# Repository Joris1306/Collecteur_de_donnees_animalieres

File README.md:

**(English part below)**

# Piège Caméra avec Classification Animale par IA (De A à Z)

Bienvenue sur le dépôt officiel du projet **Piège Photographique avec Classification Animale par IA**. Nous sommes une équipe de six étudiants ingénieurs de **Polytech Nantes** ayant dédié une année universitaire complète à la conception, fabrication et au déploiement de cette solution open-source.

Ce projet a été réalisé en partenariat étroit avec la **Mairie de Saint-Mars-du-Désert** et ses associations partenaires : le **WWF**, la **LPO** (Ligue pour la Protection des Oiseaux) et **Natura 2000**, qui ont gracieusement financé et soutenu notre démarche.

---

## 🌍 Contexte & Objectifs

La préservation de la biodiversité et la conservation des espèces sont des enjeux plus que jamais urgents. Pour protéger efficacement notre faune locale, il est indispensable de mieux la connaître et de suivre son évolution.

C'est là tout l'enjeu de notre projet : concevoir de A à Z un **piège photographique autonome couplé à une intelligence artificielle de classification**. Les données capturées sont envoyées vers un serveur centralisé et rendues accessibles à travers une interface web intuitive.

**Le but ultime :** Automatiser le recensement de la faune locale pour enrichir l'**ABC (Atlas de la Biodiversité Communale)**.

---

## 🛠️ Architecture du Projet & Contenu du Dépôt

Ce repository rassemble l'intégralité des ressources nécessaires pour reproduire et améliorer notre travail :

* **⚡ Électronique & Conception :** Les codes ESP32 du piège caméra, Modélisations 3D du boîtier, schémas électriques et liste complète des composants (BOM).
* **🧠 Intelligence Artificielle :** Algorithmes et scripts d'apprentissage pour la détection et la classification embarquée des animaux.
* **🌐 Serveur & Interface Web :** Architecture backend pour le stockage des données et code de l'interface utilisateur.
* **📄 Documentation :** Rapports techniques détaillés pour ceux qui souhaitent approfondir les choix d'ingénierie et méthodologies du projet.

---

## 🤝 Remerciements

Nous tenons à exprimer notre profonde gratitude envers :
* Nos professeurs de **Polytech Nantes** pour leur encadrement et leurs précieux conseils.
* La **Mairie de Saint-Mars-du-Désert** ainsi que les associations partenaires pour leur confiance et leur soutien financier.
* Les professionnels et chercheurs du milieu de l'environnement qui ont répondu avec enthousiasme à nos questions, prouvant que la recherche pour la biodiversité est avant tout une grande famille.

Nous passons aujourd'hui le flambeau aux futurs groupes d'étudiants passionnés. Ce projet est entièrement **open-source**, et nous avons hâte de voir comment vous saurez le faire évoluer !

---

## 🔗 Démo en Ligne

Découvrez les données récoltées et les résultats de la classification en temps réel :
👉 **[Accéder à l'Interface Web du Projet](http://90.59.66.6:5050)**

***

# Camera Trap with AI Animal Classification (From Scratch)

Welcome to the official repository for the **Camera Trap with AI Animal Classification** project. We are a team of six engineering students from **Polytech Nantes** who dedicated a full academic year to designing, building, and deploying this open-source solution. 

This project was developed in close partnership with the **Municipality of Saint-Mars-du-Désert** and its environmental partners: **WWF**, **LPO** (League for the Protection of Birds), and **Natura 2000**, who generously funded and supported our work.

---

## 🌍 Context & Vision

Biodiversity and species conservation have never been more critical. To protect our local wildlife effectively, we must first monitor and understand it. 

Our project tackles this challenge from the ground up by building an autonomous **Camera Trap paired with an AI-driven animal classification model**. Captured footage is securely transmitted to a central server and made accessible through an intuitive web interface. 

**The ultimate goal:** Automate the inventory and monitoring of local fauna to support the **ABC (Atlas de la Biodiversité Communale)** initiatives.

---

## 🛠️ Project Architecture & Repository Structure

This repository contains everything needed to replicate, understand, and build upon our work from scratch:

* **⚡ Hardware & Electronics:** ESP32 principal code, 3D CAD modeling files for the enclosure, electrical schematics, and a complete Bill of Materials (BOM).
* **🧠 Artificial Intelligence:** Embedded AI models and scripts optimized for real-time edge animal classification.
* **🌐 Server & Web Interface:** Backend architecture for data collection and frontend dashboard code for visualization.
* **📄 Documentation:** Deep-dive technical reports detailing our engineering choices, challenges, and methodologies.

---

## 🤝 Acknowledgments

We would like to extend our deepest gratitude to:
* Our supervising professors at **Polytech Nantes** for their invaluable academic guidance.
* The **Municipality of Saint-Mars-du-Désert** and its partner associations for their trust and financial backing.
* The biodiversity and research professionals who generously shared their expertise with us. Your willingness to help proves that wildlife conservation is a truly collaborative family.

We now pass the torch to future generations of passionate students. This project is entirely **open-source**, and we look forward to seeing how you adapt, improve, and scale it!

---

## 🔗 Live Demo

Explore the captured data and classification metrics live here:
👉 **[Access the Web Interface Dashboard](http://90.59.66.6:5050)**

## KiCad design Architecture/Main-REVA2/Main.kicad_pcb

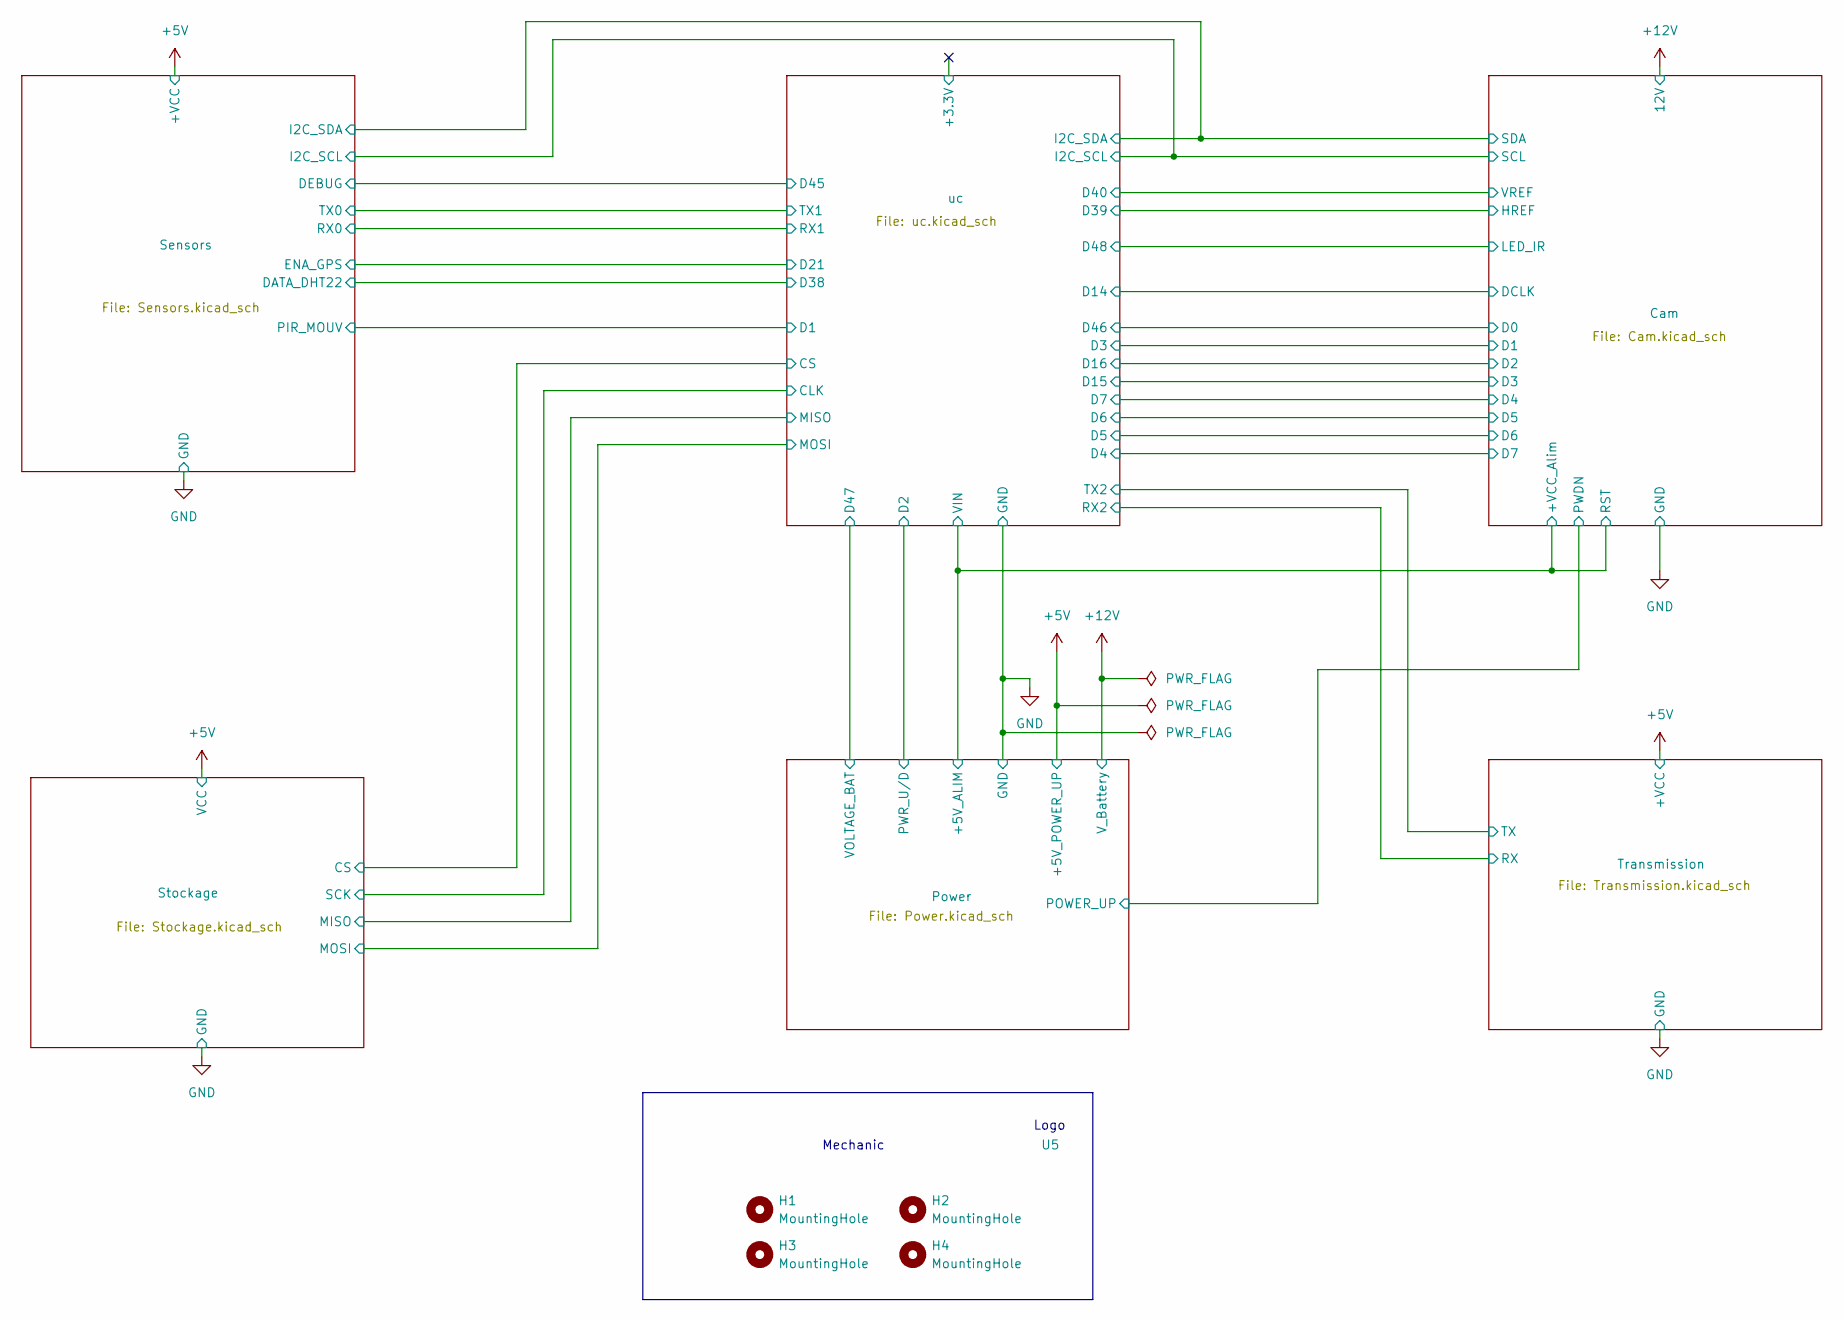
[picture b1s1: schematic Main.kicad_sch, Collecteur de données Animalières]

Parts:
H1, H2, H3, H4: MountingHole; MountingHole_2.2mm_M2_ISO7380
U5: Logo_20_20

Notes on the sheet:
Mechanic
Logo

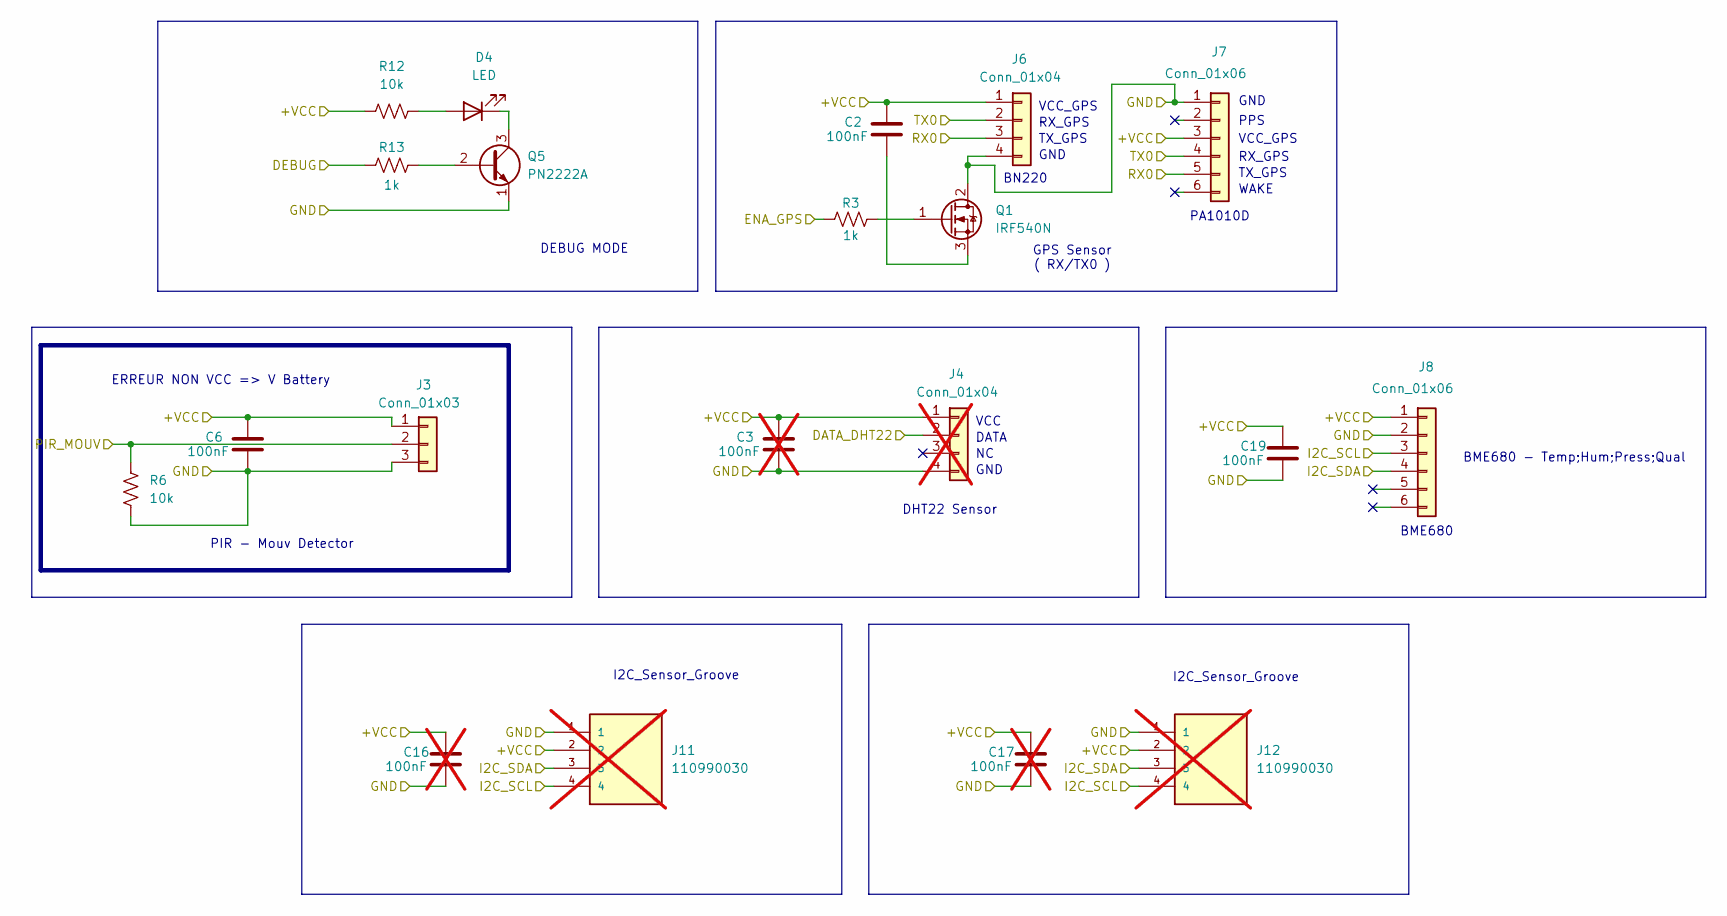
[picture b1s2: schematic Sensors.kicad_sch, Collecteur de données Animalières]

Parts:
C2, C6, C19: 100nF; C_Disc_D5.0mm_W2.5mm_P5.00mm
C3, C16, C17: 100nF; C_Disc_D5.0mm_W2.5mm_P5.00mm; not fitted
D4: LED; LED_D5.0mm
J3: Conn_01x03; PinHeader_1x03_P2.54mm_Vertical
J4: Conn_01x04; PinHeader_1x04_P2.54mm_Vertical; not fitted
J6: Conn_01x04; PinHeader_1x04_P2.54mm_Vertical
J7, J8: Conn_01x06; PinHeader_1x06_P2.54mm_Vertical
J11, J12: 110990030; Grove; PARTREV A; not fitted
Q1: IRF540N; TO-220-3_Vertical
Q5: PN2222A; TO-92_Inline
R3, R13: 1k; R_Axial_DIN0207_L6.3mm_D2.5mm_P10.16mm_Horizontal
R6, R12: 10k; R_Axial_DIN0207_L6.3mm_D2.5mm_P10.16mm_Horizontal

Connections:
+5V: C2.1, C3.1, C6.1, C16.1, C17.1, C19.1, J3.1, J4.1, J6.1, J7.3, J8.1, J11.2, J12.2, R12.1; also elsewhere on the board
/Cam/SCL: J8.3, J11.4, J12.4; also elsewhere on the board
/Cam/SDA: J8.4, J11.3, J12.3; also elsewhere on the board
/Sensors/DATA_DHT22: J4.2; also elsewhere on the board
/Sensors/DEBUG: R13.1; also elsewhere on the board
/Sensors/ENA_GPS: R3.1; also elsewhere on the board
/Sensors/PIR_MOUV: J3.2, R6.1; also elsewhere on the board
/Sensors/RX0: J6.3, J7.5; also elsewhere on the board
/Sensors/TX0: J6.2, J7.4; also elsewhere on the board
GND: C3.2, C6.2, C16.2, C17.2, C19.2, J3.3, J4.4, J6.4, J7.1, J8.2, J11.1, J12.1, Q1.2 (D), Q5.1 (E), R6.2; also elsewhere on the board
unnamed: D4.2 (A), R12.2
unnamed: D4.1 (K), Q5.3 (C)
unnamed: Q1.1 (G), R3.2
unnamed: C2.2, Q1.3 (S)
unnamed: Q5.2 (B), R13.2

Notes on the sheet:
RX_GPS
I2C_Sensor_Groove
PA1010D
VCC
GND
VCC_GPS
PIR - Mouv Detector
DATA
TX_GPS
DEBUG MODE
BME680
BN220
ERREUR NON VCC => V Battery
PPS
GPS Sensor ( RX/TX0 )
WAKE
BME680 - Temp;Hum;Press;Qual
DHT22 Sensor

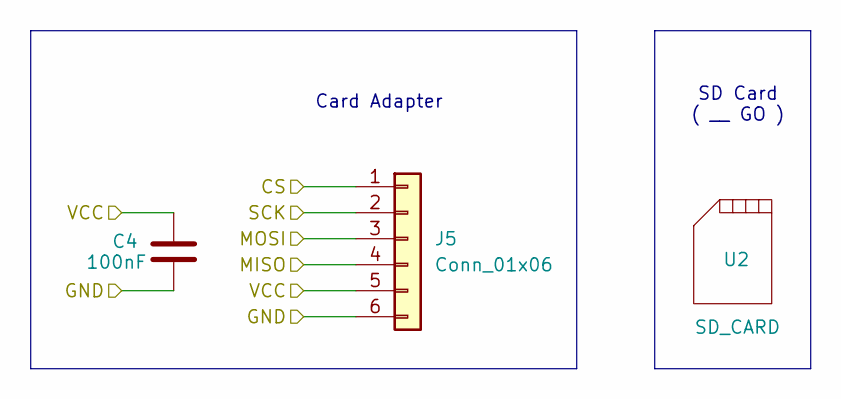
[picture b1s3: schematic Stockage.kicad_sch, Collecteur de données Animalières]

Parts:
C4: 100nF; C_Disc_D5.0mm_W2.5mm_P5.00mm
J5: Conn_01x06; PinHeader_1x06_P2.54mm_Vertical
U2: SD_CARD

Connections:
+5V: C4.1, J5.5; also elsewhere on the board
/Stockage/CS: J5.1; also elsewhere on the board
/Stockage/MISO: J5.4; also elsewhere on the board
/Stockage/MOSI: J5.3; also elsewhere on the board
/Stockage/SCK: J5.2; also elsewhere on the board
GND: C4.2, J5.6; also elsewhere on the board

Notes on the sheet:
SD Card ( __ GO )
Card Adapter

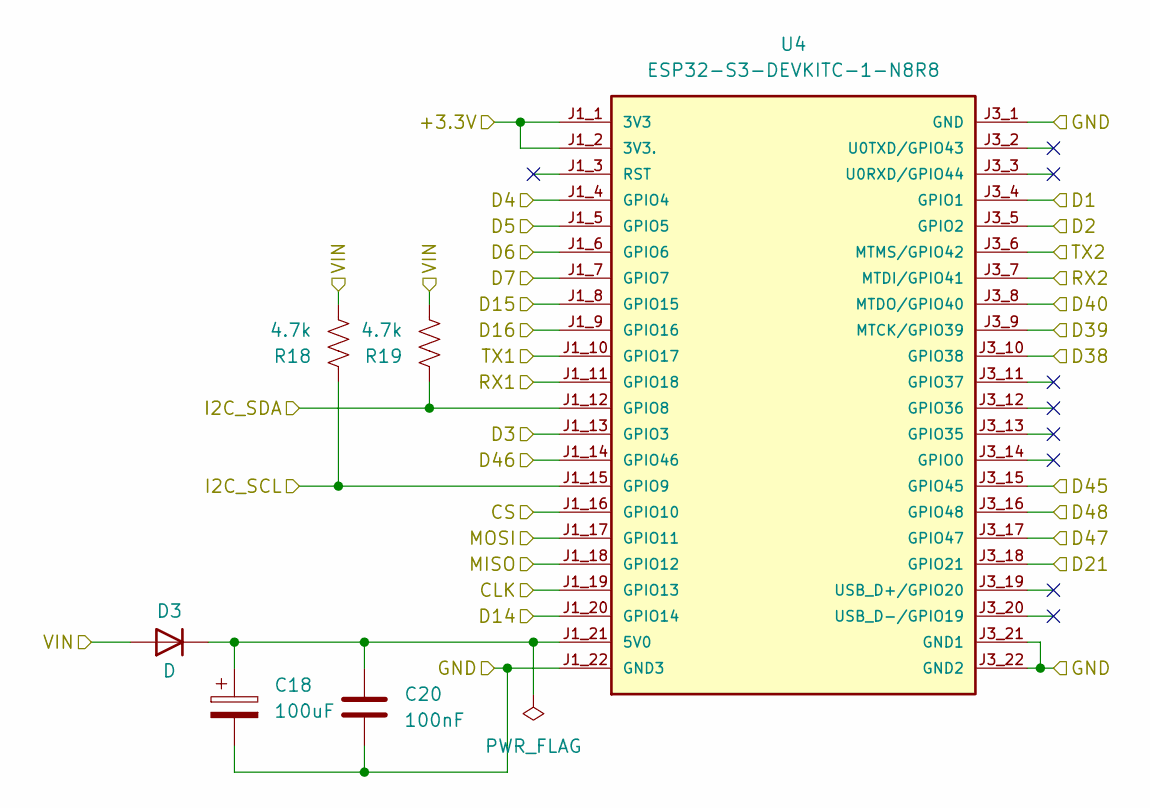
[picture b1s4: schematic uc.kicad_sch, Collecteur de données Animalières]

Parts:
C18: 100uF; C_Radial_D10.0mm_H16.0mm_P5.00mm
C20: 100nF; C_Disc_D5.0mm_W2.5mm_P5.00mm
D3: D; D_DO-35_SOD27_P7.62mm_Horizontal
R18, R19: 4.7k; R_Axial_DIN0207_L6.3mm_D2.5mm_P10.16mm_Horizontal
U4: ESP32-S3-DEVKITC-1-N8R8

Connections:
/Cam/+VCC_Alim: D3.2 (A), R18.2, R19.2; also elsewhere on the board
/Cam/D0: U4.J1_14 (GPIO46); also elsewhere on the board
/Cam/D1: U4.J1_13 (GPIO3); also elsewhere on the board
/Cam/D2: U4.J1_9 (GPIO16); also elsewhere on the board
/Cam/D3: U4.J1_8 (GPIO15); also elsewhere on the board
/Cam/D4: U4.J1_7 (GPIO7); also elsewhere on the board
/Cam/D5: U4.J1_6 (GPIO6); also elsewhere on the board
/Cam/D6: U4.J1_5 (GPIO5); also elsewhere on the board
/Cam/D7: U4.J1_4 (GPIO4); also elsewhere on the board
/Cam/DCLK: U4.J1_20 (GPIO14); also elsewhere on the board
/Cam/HREF: U4.J3_9 (MTCK/GPIO39); also elsewhere on the board
/Cam/LED_IR: U4.J3_16 (GPIO48); also elsewhere on the board
/Cam/SCL: R18.1, U4.J1_15 (GPIO9); also elsewhere on the board
/Cam/SDA: R19.1, U4.J1_12 (GPIO8); also elsewhere on the board
/Cam/VREF: U4.J3_8 (MTDO/GPIO40); also elsewhere on the board
/Power/PWR_U/D: U4.J3_5 (GPIO2); also elsewhere on the board
/Power/VOLTAGE_BAT: U4.J3_17 (GPIO47); also elsewhere on the board
/Sensors/DATA_DHT22: U4.J3_10 (GPIO38); also elsewhere on the board
/Sensors/DEBUG: U4.J3_15 (GPIO45); also elsewhere on the board
/Sensors/ENA_GPS: U4.J3_18 (GPIO21); also elsewhere on the board
/Sensors/PIR_MOUV: U4.J3_4 (GPIO1); also elsewhere on the board
/Sensors/RX0: U4.J1_11 (GPIO18); also elsewhere on the board
/Sensors/TX0: U4.J1_10 (GPIO17); also elsewhere on the board
/Stockage/CS: U4.J1_16 (GPIO10); also elsewhere on the board
/Stockage/MISO: U4.J1_18 (GPIO12); also elsewhere on the board
/Stockage/MOSI: U4.J1_17 (GPIO11); also elsewhere on the board
/Stockage/SCK: U4.J1_19 (GPIO13); also elsewhere on the board
/Transmission/RX: U4.J3_7 (MTDI/GPIO41); also elsewhere on the board
/Transmission/TX: U4.J3_6 (MTMS/GPIO42); also elsewhere on the board
/uc/+3.3V: U4.J1_1 (3V3), U4.J1_2 (3V3.)
GND: C18.2, C20.2, U4.J1_22 (GND3), U4.J3_1 (GND), U4.J3_21 (GND1), U4.J3_22 (GND2); also elsewhere on the board
unnamed: C18.1, C20.1, D3.1 (K), U4.J1_21 (5V0)

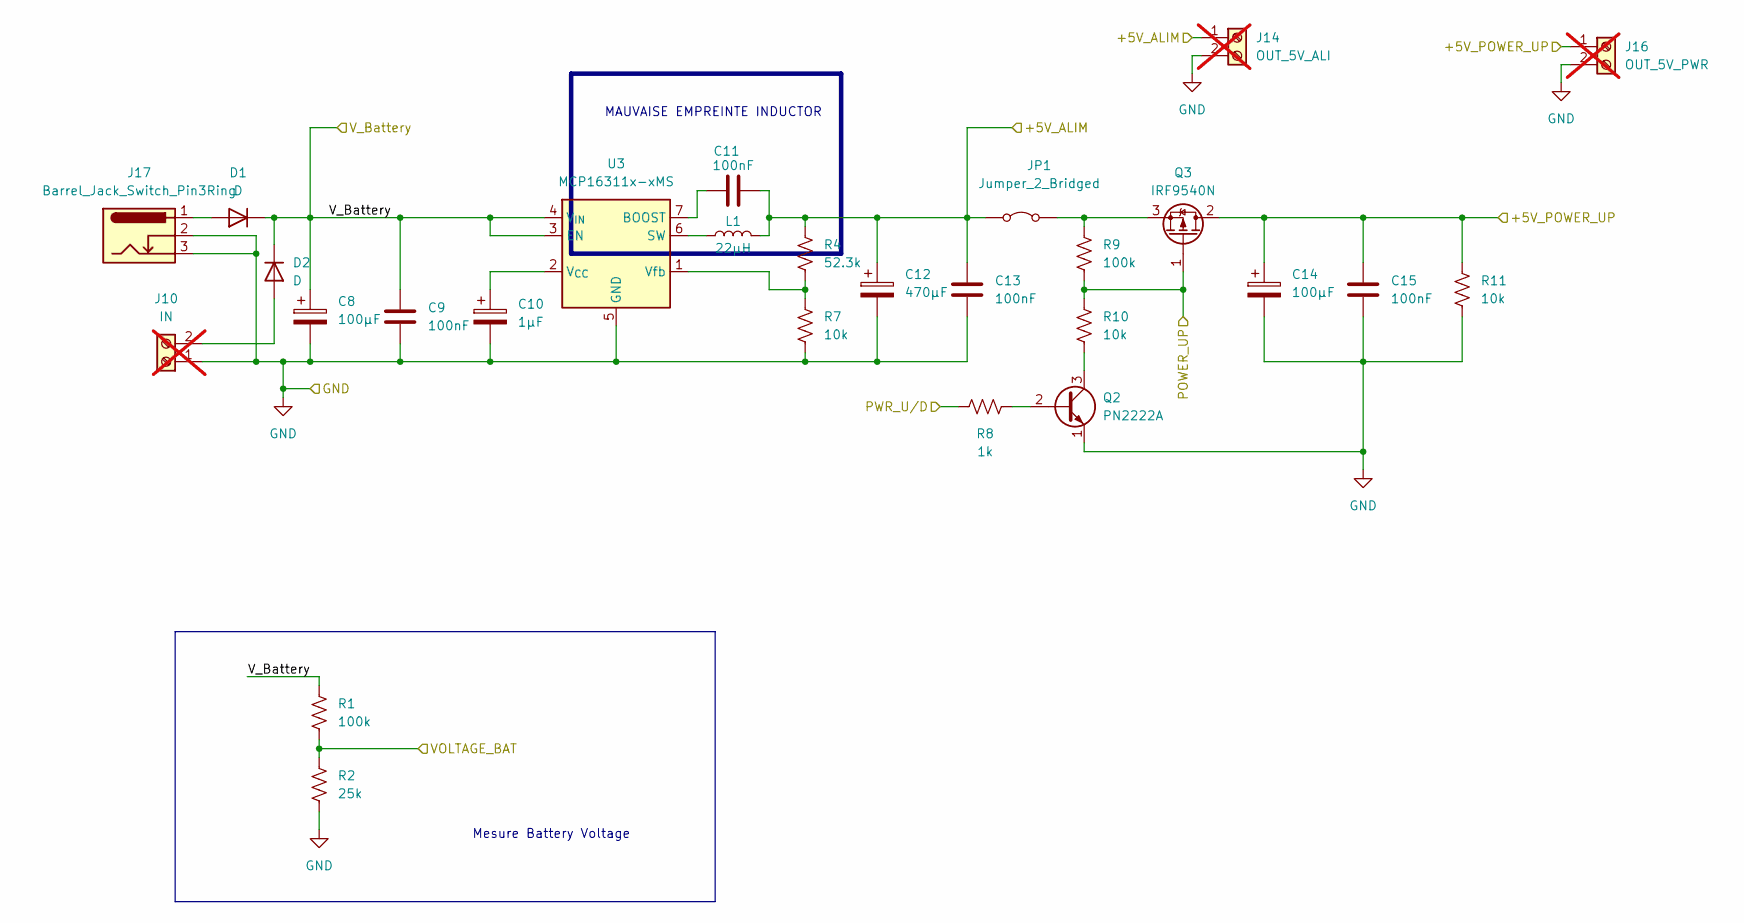
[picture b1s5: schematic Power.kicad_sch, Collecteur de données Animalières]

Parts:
C8, C14: 100µF; C_Radial_D10.0mm_H16.0mm_P5.00mm
C9, C11, C13, C15: 100nF; C_Disc_D5.0mm_W2.5mm_P5.00mm
C10: 1µF; C_Radial_D10.0mm_H16.0mm_P5.00mm
C12: 470µF; C_Radial_D10.0mm_H16.0mm_P5.00mm
D1, D2: D; D_DO-35_SOD27_P7.62mm_Horizontal
J10: IN; PinHeader_1x02_P2.54mm_Vertical; not fitted
J14: OUT_5V_ALI; PinHeader_1x02_P2.54mm_Vertical; not fitted
J16: OUT_5V_PWR; PinHeader_1x02_P2.54mm_Vertical; not fitted
J17: Barrel_Jack_Switch_Pin3Ring; BarrelJack_Horizontal
JP1: Jumper_2_Bridged; PinHeader_1x02_P2.54mm_Vertical
L1: 22µH; R_Axial_DIN0207_L6.3mm_D2.5mm_P10.16mm_Horizontal
Q2: PN2222A; TO-92_Inline
Q3: IRF9540N; TO-220-3_Vertical
R1, R9: 100k; R_Axial_DIN0207_L6.3mm_D2.5mm_P10.16mm_Horizontal
R2: 25k; R_Axial_DIN0207_L6.3mm_D2.5mm_P10.16mm_Horizontal
R4: 52.3k; R_Axial_DIN0207_L6.3mm_D2.5mm_P10.16mm_Horizontal
R7, R10, R11: 10k; R_Axial_DIN0207_L6.3mm_D2.5mm_P10.16mm_Horizontal
R8: 1k; R_Axial_DIN0207_L6.3mm_D2.5mm_P10.16mm_Horizontal
U3: MCP16311x-xMS; MSOP-8_3x3mm_P0.65mm

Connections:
+5V: C14.1, C15.1, J16.1, Q3.2 (D), R11.1; also elsewhere on the board
+12V: C8.1, C9.1, D1.1 (K), D2.1 (K), R1.1, U3.3 (EN), U3.4 (V_{IN}); also elsewhere on the board
/Cam/+VCC_Alim: C11.2, C12.1, C13.1, J14.1, JP1.1 (A), L1.2, R4.1; also elsewhere on the board
/Cam/PWDN: Q3.1 (G), R9.2, R10.1; also elsewhere on the board
/Power/PWR_U/D: R8.1; also elsewhere on the board
/Power/VOLTAGE_BAT: R1.2, R2.1; also elsewhere on the board
GND: C8.2, C9.2, C10.2, C12.2, C13.2, C14.2, C15.2, J10.1, J14.2, J16.2, J17.2, J17.3, Q2.1 (E), R2.2, R7.2, R11.2, U3.5 (GND), U3.8 (GND); also elsewhere on the board
unnamed: D1.2 (A), J17.1
unnamed: D2.2 (A), J10.2
unnamed: JP1.2 (B), Q3.3 (S), R9.1
unnamed: Q2.2 (B), R8.2
unnamed: Q2.3 (C), R10.2
unnamed: C11.1, U3.7 (BOOST)
unnamed: L1.1, U3.6 (SW)
unnamed: C10.1, U3.2 (V_{CC})
unnamed: R4.2, R7.1, U3.1 (Vfb)

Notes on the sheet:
MAUVAISE EMPREINTE INDUCTOR
Mesure Battery Voltage

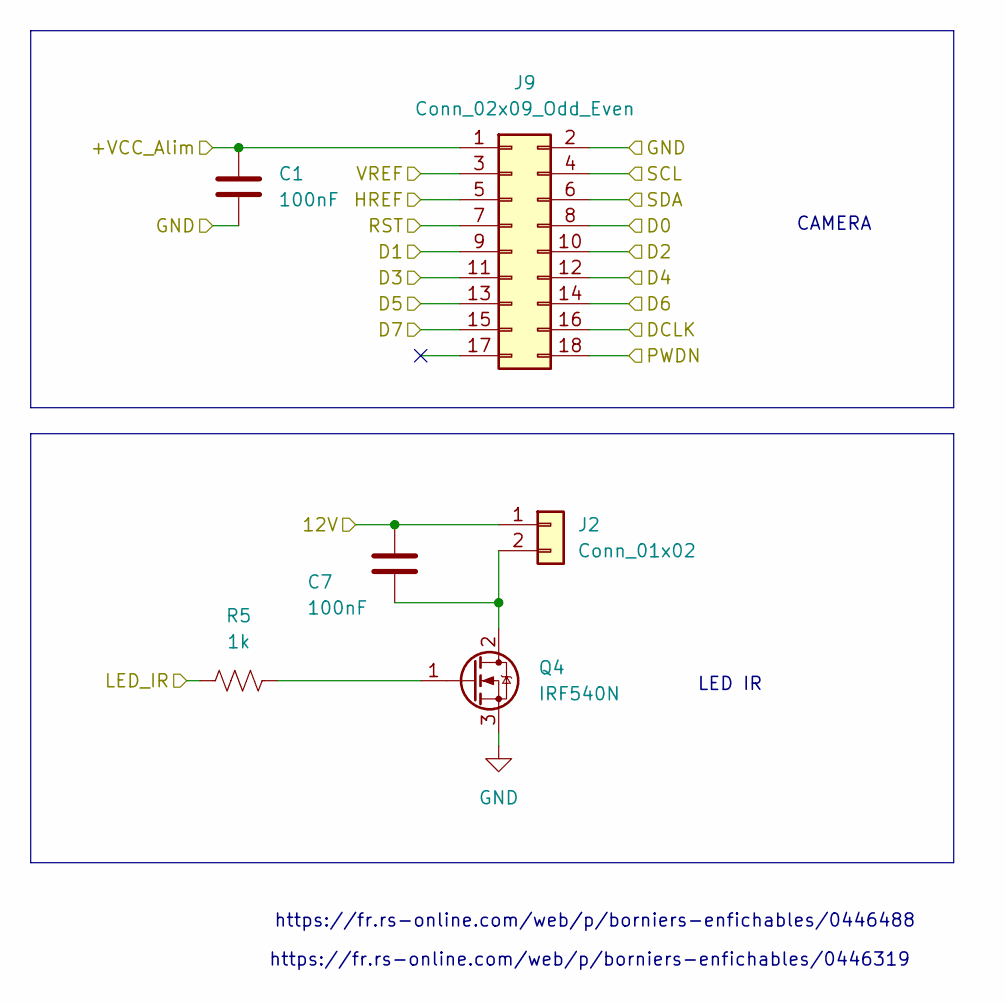
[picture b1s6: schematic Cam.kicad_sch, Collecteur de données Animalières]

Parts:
C1, C7: 100nF; C_Disc_D5.0mm_W2.5mm_P5.00mm
J2: Conn_01x02; PinHeader_1x02_P2.54mm_Vertical
J9: Conn_02x09_Odd_Even; OV2640
Q4: IRF540N; TO-220-3_Horizontal_TabDown
R5: 1k; R_Axial_DIN0207_L6.3mm_D2.5mm_P10.16mm_Horizontal

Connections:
+12V: C7.1, J2.1; also elsewhere on the board
/Cam/+VCC_Alim: C1.1, J9.1, J9.7; also elsewhere on the board
/Cam/D0: J9.8; also elsewhere on the board
/Cam/D1: J9.9; also elsewhere on the board
/Cam/D2: J9.10; also elsewhere on the board
/Cam/D3: J9.11; also elsewhere on the board
/Cam/D4: J9.12; also elsewhere on the board
/Cam/D5: J9.13; also elsewhere on the board
/Cam/D6: J9.14; also elsewhere on the board
/Cam/D7: J9.15; also elsewhere on the board
/Cam/DCLK: J9.16; also elsewhere on the board
/Cam/HREF: J9.5; also elsewhere on the board
/Cam/LED_IR: R5.1; also elsewhere on the board
/Cam/PWDN: J9.18; also elsewhere on the board
/Cam/SCL: J9.4; also elsewhere on the board
/Cam/SDA: J9.6; also elsewhere on the board
/Cam/VREF: J9.3; also elsewhere on the board
GND: C1.2, J9.2, Q4.3 (S); also elsewhere on the board
unnamed: C7.2, J2.2, Q4.2 (D)
unnamed: Q4.1 (G), R5.2

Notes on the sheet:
LED IR
https://fr.rs-online.com/web/p/borniers-enfichables/0446319
CAMERA
https://fr.rs-online.com/web/p/borniers-enfichables/0446488

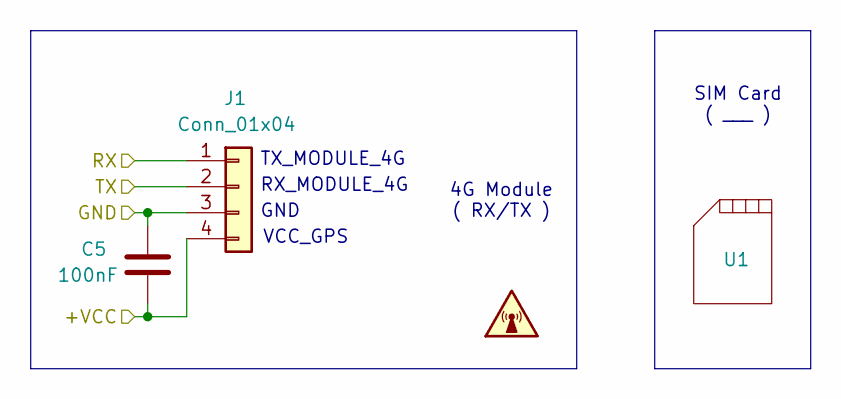
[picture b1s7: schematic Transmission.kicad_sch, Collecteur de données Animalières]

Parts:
C5: 100nF; C_Disc_D5.0mm_W2.5mm_P5.00mm
J1: Conn_01x04; PinHeader_1x04_P2.54mm_Vertical
U1: (no value)

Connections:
+5V: C5.2, J1.4; also elsewhere on the board
/Transmission/RX: J1.1; also elsewhere on the board
/Transmission/TX: J1.2; also elsewhere on the board
GND: C5.1, J1.3; also elsewhere on the board

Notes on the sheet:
SIM Card ( ___ )
GND
4G Module ( RX/TX )
RX_MODULE_4G
VCC_GPS
TX_MODULE_4G

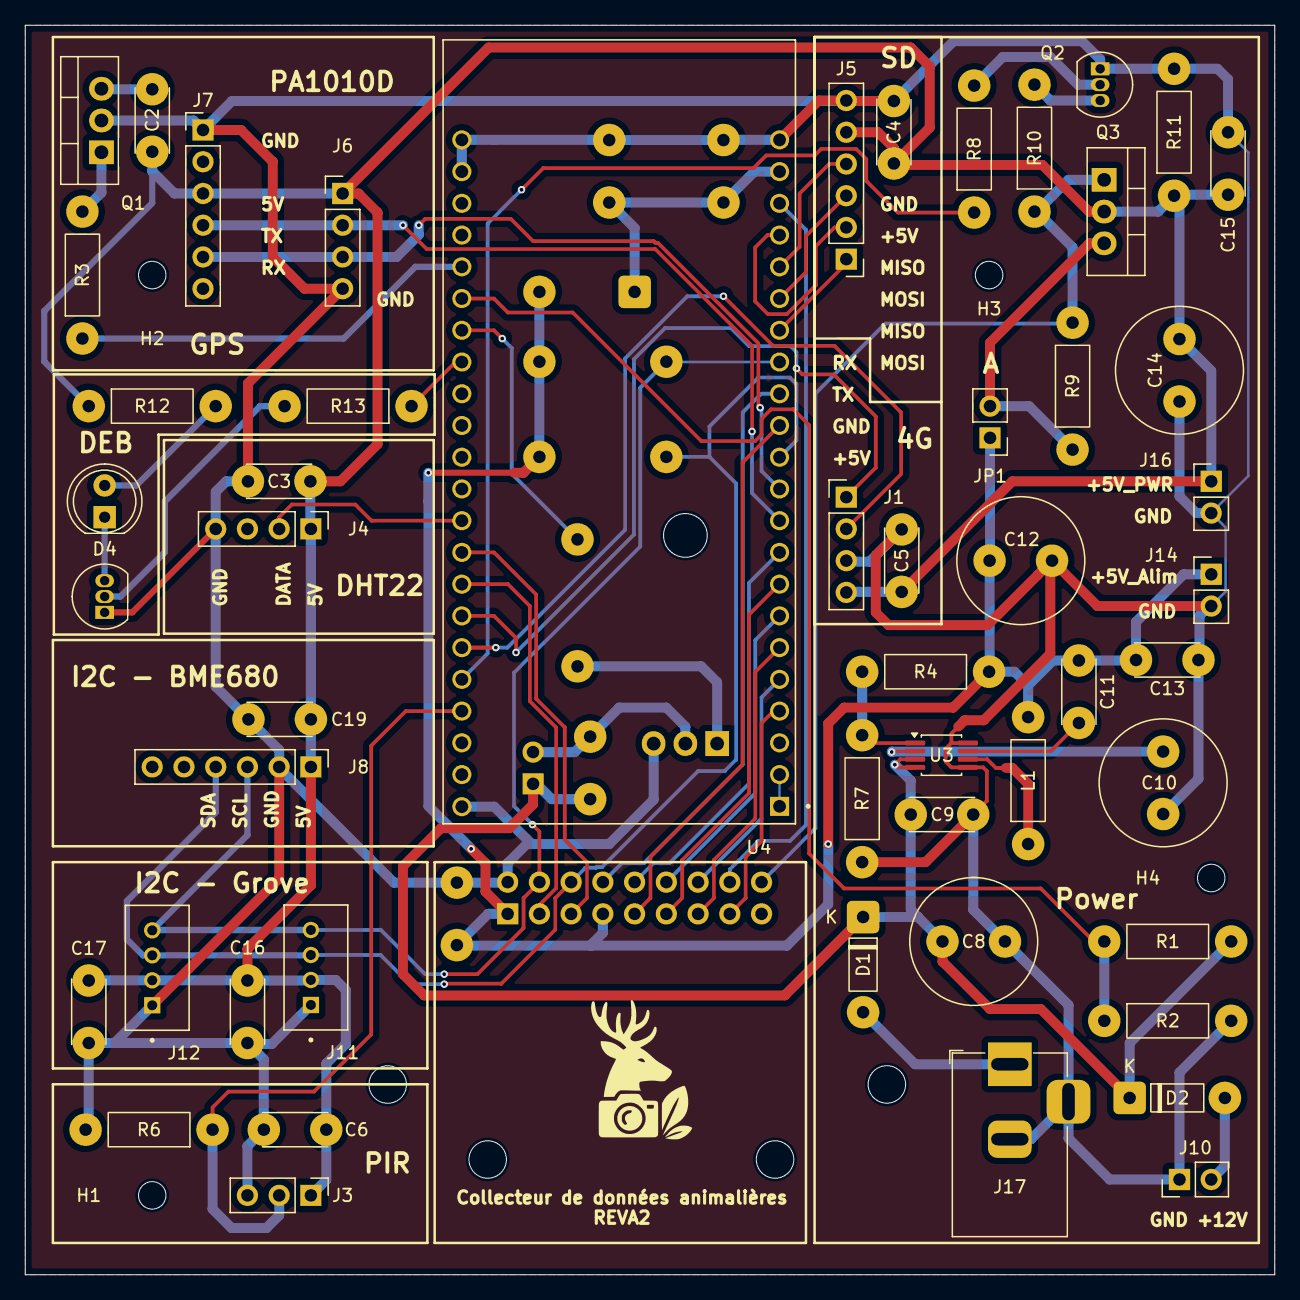
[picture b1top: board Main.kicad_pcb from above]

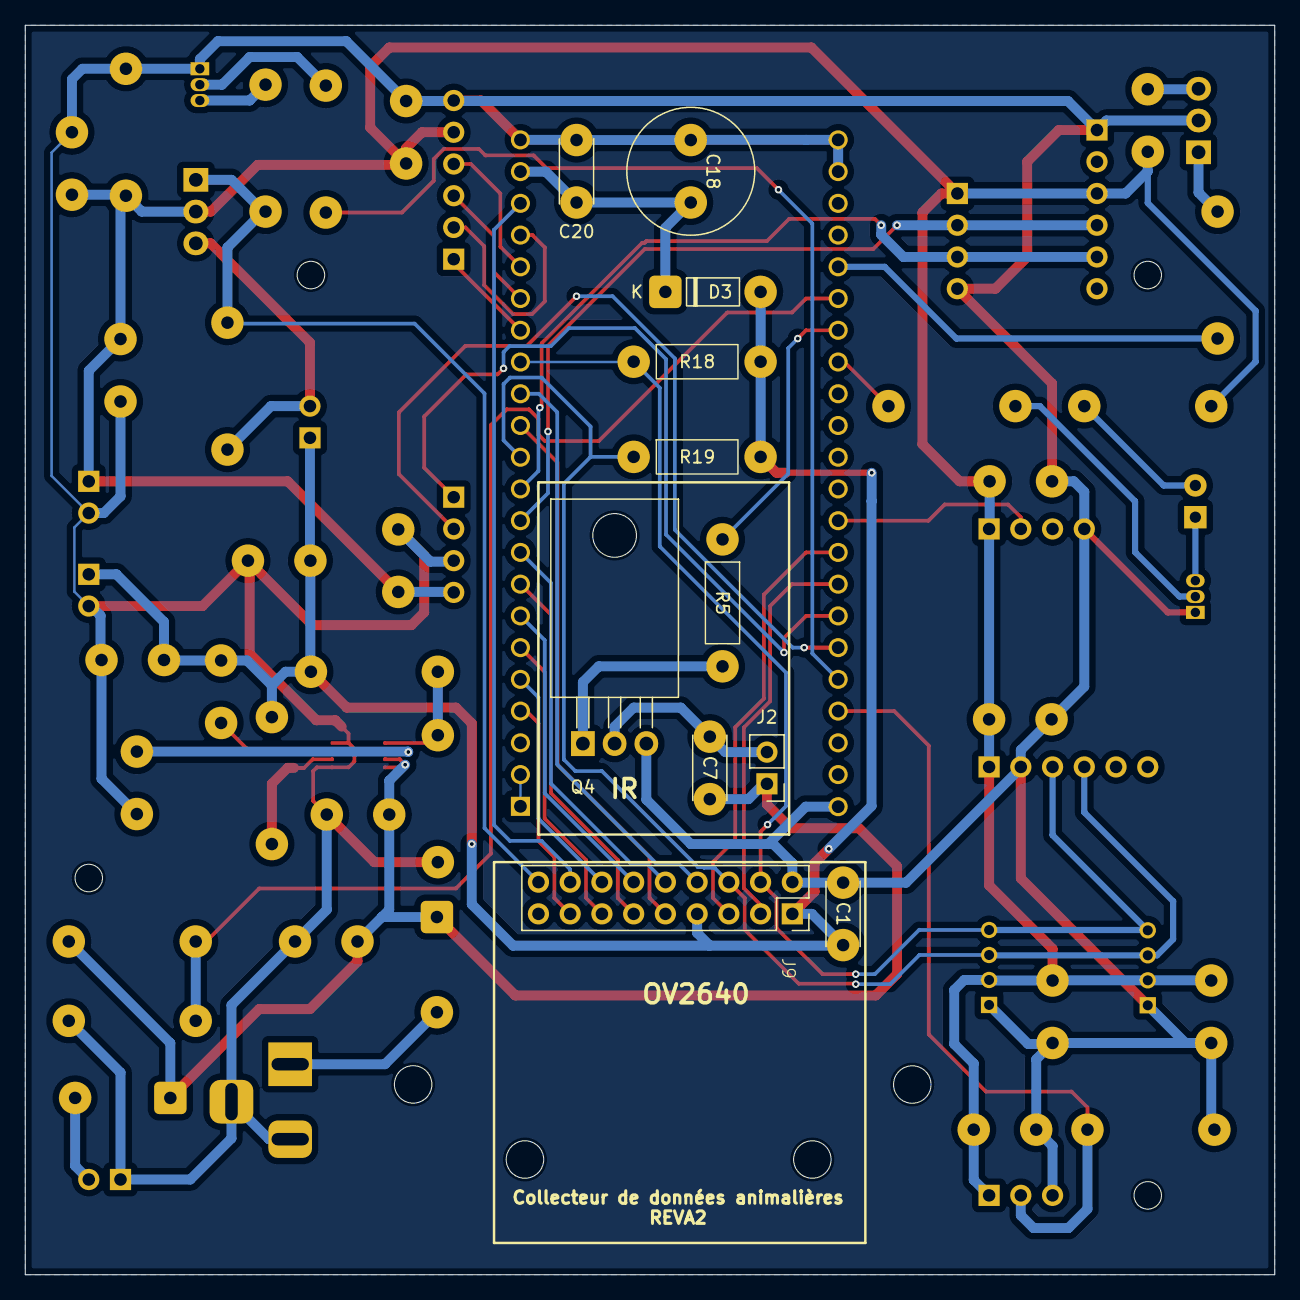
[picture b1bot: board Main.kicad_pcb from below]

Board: 2 copper layers, 100.0 x 100.0 mm, 68 parts (11 on the bottom side), 51 nets.

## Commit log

2025-10-17 Modif CDC Nolan
2025-10-17 Modif CDC
2025-10-30 ajout de TEDS.tex (paragraphe teds demander par ewen)
2025-11-01 .gitignore : ne pas mettre en suivi les fichiers temporaires produit par le latex
2025-11-01 modification .gitignore
2025-11-01 Commit CDC v2
2025-11-02 supp CDC/.gitignore (inutile)
2025-11-02 supp des fichiers temp
2025-11-02 .gitignore remis
2025-11-05 ajout de la fonction stockage distant
2025-11-05 mise a jour des fonctionnalitées principales
2025-11-05 Commit CDC
2025-11-05 Modif gitignore
2025-11-13 Version final V2
2026-01-18 Add project title to README
2026-01-18 Ajout de plein de bonne chose, il y a les différents fichier source pour faire le programme final de stockage disant
2026-01-19 Add TO-DO list for project tasks
2026-01-21 Add new tasks to the TO-DO list
2026-01-23 Update TO-DO list with completed and new tasks
    Updated the TO-DO list to mark completed tasks and add new items.
2026-01-23 Mise à jour stockage distant, ajout fonction login, suppression image (depuis python), ajout d'une page home
2026-01-23 Ajout état image
2026-01-25 "Refactof avec le dossier APP qui contient toutes les librairies/programme pour faire tourner le stockage distant"
2026-01-26 Rename 2026-01-04_15:40:44.png to test1.png
2026-01-26 Rename 2026-01-04_22:34:38.png to test2.png
2026-01-26 Rename 2026-01-07_22:11:27.png to test3.png
2026-01-26 Rename 2026-01-07_22:12:19.png to test4.png
2026-01-26 Rename 2026-01-07_22:12:30.png to test5.png
2026-01-26 Rename test1.png to 2026-01-04_15:40:44.png
2026-01-26 Rename test2.png to 2026-01-04_22:34:38.png
2026-01-26 Rename test3.png to 2026-01-07_22:11:27.png
2026-01-26 Rename test4.png to 2026-01-07_22:12:19.png
2026-01-26 Rename test5.png to 026-01-07_22:12:30.png
2026-01-27 refactor avec les fonctionnalités de privileges pour cacher les images cachées pour un simple utilisateur
2026-01-27 rename de toutes les images et ajout de style pour les filtrages et export
2026-01-27 suppression image avec : dans le nom
2026-01-27 Add openpyxl installation to Liste_lib.txt
2026-01-28 ajout d'un onglet de journal (avec listes des événements), modification de la page des batteries (ergonomie) et une fausse class IA_CLASSIFICATION
2026-01-29 mise à jour de la carte avec les pièges camera, mise à jour de la journalisation des evenements, mise à jour de la page caché pour affiiché aussi les etat 'null'
2026-01-29 Remove __pycache__, .vscode, and .idea from tracking and update .gitignore
2026-01-29 Clear git cache and re-apply .gitignore
2026-01-30 Ajout des fonction IA (get_etat, get_image_traite, get_animal_name), fonctionnel que pour la detection et classification d'humain.
2026-01-30 Add ultralytics installation command
2026-02-01 mise à jour de la base de donnée avec de nouvelles données, mise à jour de l'IA
2026-02-02 Update TO-DO list with completed and new tasks
    Updated the TO-DO list by marking several tasks as completed and adding new tasks.
2026-02-02 Mise à jour de l'ia
2026-02-02 Modification du fichier "AI_CLASSIFICATION.py". Pour changement d'état et traitement image en paramètre globaux. Pour chaque détection on a egalement : ANIMAL,CONFIANCE.
2026-02-04 Remove tracked app.db and images from git
2026-02-04 update : bdd inclut une table ia avec la liste des reconnaissances des différentes identifications + affichage sur la base de donnée
2026-02-13 Update button functionality in /main/hidden
    Transform hide button in /main/hidden to show button for better functionality.
2026-02-13 Update TO-DO list with new tasks and completed items
2026-02-16 "update des fonctions de langues"
2026-02-17 Add link to the site in README
2026-03-03 Mise à jour des librairies pour des erreurs de typages, etc.
2026-03-03 update IA avec Speciesnet
2026-03-31 ajout d'image de test pic*, correction des scripts pour affiché les différentes détection au sein d'une seule image
2026-03-31 mise à jour de AI_CLASSIFICATION.py
2026-04-29 update final
2026-05-15 déploiment sur un pseudo serveur distant (local)
2026-06-03 Revise README for project overview and details
    Updated the README to provide detailed project information, context, architecture, acknowledgments, and live demo links in both English and French.
2026-06-03 Update README to include ESP32 principal code
2026-06-03 Enhance README with ESP32 code details
    Updated the electronics and design section to include ESP32 codes.
2026-06-03 Add English version and project information
    Added English translation and updated project details.
